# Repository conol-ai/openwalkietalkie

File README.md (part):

# Cohdl OpenWalkieTalkie

[Website and downloads](https://openwalkietalkie.org/) ·
[Latest release](https://github.com/conol-ai/openwalkietalkie/releases/latest)

Firmware and [routed BodyV5 r3 hardware design](hardware/rev-a/README.md) for
OpenWalkieTalkie, a handheld with a touch screen, a scroll wheel, PTT, Enter,
Esc, Shift and two front macro keys. The custom hardware includes a four-layer main PCB and
two-layer encoder PCB, with matching fabrication files and populated 3D models.

The firmware turns the device into the **Agent Command Deck**: a handheld
status board and radio for someone running several AI agent sessions at once.
The screen shows who needs you, PTT talks to the active agent, and the buttons
answer questions and switch channels.

The Rust / [embassy](https://embassy.dev) firmware currently runs on a **LilyGo
T-Display SF32** development board, which carries a SiFli **SF32LB52x** (Cortex-M33,
16MB NOR, 8MB PSRAM) and the same class of 2.16" CO5300 AMOLED with CST9220
touch. The dev board has no scroll wheel, so the **T-SF32-Keyboard** expansion
stands in for the wheel and buttons.

Sibling to [`openmicrokbd`](https://github.com/conol-ai/openmicrokbd) (v1,
STM32F072) — same approach, different silicon.

## What works today

Boot, the debug UART, the shared I2C bus, keypad and touchscreen input,
battery charging, and the Agent Command Deck's 480x480 UI on the AMOLED:
five faces, the face manager, notifications, the PTT LISTENING overlay and a
built-in demo host. Everything above the drivers is covered by host tests and
rendered previews; **none of the deck has been validated on hardware yet**
(see the [first-flash checklist](docs/deck-device-checklist.md)).

The deck is its own USB/BLE HID device: **Cohdl OpenWalkieTalkie**, VID
`0x1209` PID `0x5754`, one vendor collection (usage page `0xFF00`, report id
6, 64-byte reports). Report channel 2 carries a small system RPC
(`sys.version`, `sys.reboot`, `device.status`); the deck faces talk to a deck
host over channel 5 of the same connection ([deck protocol](#the-deck-host)).

The `1209:5754` allocation has been requested in
[pid.codes PR #1312](https://github.com/pidcodes/pidcodes.github.com/pull/1312)
and is pending registry approval. Application firmware and USB recovery use
the same product ID.

Pair **OpenWalkieTalkie** in macOS Bluetooth settings. The latest computer's bond
key and HID/battery notification preferences are stored in an append-only
flash journal at `0x12710000..0x1271FFFF`, reserved from the application
linker region. Automatic encrypted reconnection after a firmware update has
been verified. Upgrading from firmware that kept keys only in RAM requires
forgetting the old device and pairing once to create the persistent bond.

The journal checks each record's version and CRC, skips torn writes, and
verifies writes by reading them back. It supports 1024 changed records and
never erases flash; an exhausted journal reports a storage error. Unchanged
keys/preferences do not consume records. `tools/flash.sh` writes ELF load
segments and preserves the reserved journal. A whole-chip erase does not.
The Embassy target carries controls, deck traffic and battery status over HID.
On Rev A it also carries the microphone and speaker, as its own BLE GATT
service on the same link rather than as a Bluetooth audio device: a PTT press
streams 16 kHz IMA ADPCM to the host, and the host's spoken replies come back
the same way (`docs/deck-protocol.md`, "Voice"). Over the USB cable the same
frames ride report channel 7 of the HID collection, so a deck on the cable
alone has its voice too, with no pairing; `deckd` uses the cable whenever it
is there and Bluetooth otherwise. The
[native audio target](native/README.md) instead presents the display board's
microphone and speaker as Bluetooth Classic audio (HFP/A2DP) alongside the
same UI.
Both targets show the website's pixel-radio icon and stacked OpenWalkieTalkie
title on a black boot splash, with a small COHDL mark and “A COHDL PROJECT”
credit. After 1.2 seconds, the Agents face appears.
The same radio appears in Settings → About and in the Mac app, Dock, menu bar
and updater. Regenerate the desktop assets with `python3 tools/generate-branding.py`
(Pillow); normal builds use the checked-in images.

Embassy boot log, abridged:

```
SFBL
openwalkietalkie-fw 0.1.0
board: LilyGo T-Display SF32 (dev)
board: holding power rail (PA41)
board: bringing up I2C1 (SCL PA38 / SDA PA37) at 400000 Hz
display: CO5300 initialised (480x480, rotation=0deg)
board: display ready
board: ready
boot: OpenWalkieTalkie splash ready
boot: I2C1 before keyboard power-up:
  0x22 XL9555 GPIO expander (keyboard board)
  0x25 AW21009 keypad LED driver (keyboard board)
  0x34 TCA8418 keypad scanner (keyboard board)
app: Agent Command Deck ready
keypad: TCA8418 ready (5x4 matrix), PA11 interrupt + 50ms fallback
```

## Install on Omarchy (Linux)

On an [Omarchy](https://omarchy.org/) (Hyprland) laptop, the deck drives the
desktop and your coding agents with no Mac involved. It shows your
workspaces and windows on the Omarchy face, and your Claude Code, Codex and
Kimi Code sessions on the roster. A PTT press on a session types the
recognised words into its terminal. Two systemd user services do it:
`deckd`, built for Linux, and the Omarchy bridge in
[`host/omarchy/`](host/omarchy/README.md); the companion app, the same window
as on a Mac, goes in Omarchy's app launcher. There is no Linux download yet:
build from source (about ten minutes the first time). The step-by-step guide
is at [openwalkietalkie.org/docs/omarchy](https://openwalkietalkie.org/docs/omarchy/).

```sh
sudo pacman -S --needed base-devel git rustup cmake clang espeak-ng wtype
rustup default stable
git clone https://github.com/conol-ai/openwalkietalkie.git
cd openwalkietalkie/host
cargo build --release --target x86_64-unknown-linux-gnu -p deckd -p openwalkietalkie-app
sh omarchy/install.sh target/x86_64-unknown-linux-gnu/release/deckd \
    target/x86_64-unknown-linux-gnu/release/openwalkietalkie-app

# Once, as root: let deckd open the deck (USB-C and Bluetooth alike)
sudo install -m 644 omarchy/70-openwalkietalkie.rules /etc/udev/rules.d/
sudo udevadm control --reload && sudo udevadm trigger --subsystem-match=hidraw

# Put your sessions on the deck (sessions already open need a restart)
python3 omarchy/omarchy_hook.py install claude   # and codex, kimi
```

Then connect the deck with USB-C, or pair **OpenWalkieTalkie** over
Bluetooth, and check that the `link:` line says `Connected, session Live`
when you run `deckd status`, or open **OpenWalkieTalkie** from the app launcher.

- **Voice:** if Superwhisper (Omarchy's dictation) is set up, it recognises
  presses with no extra setup. Otherwise download the local Whisper model:
  see [Voice](host/omarchy/README.md#voice-ptt).
- **Macropad keys that trigger Omarchy's Super shortcuts** need
  `/dev/uinput`. `install.sh` prints the optional root steps.
- **Claude usage bars** on the Usage face:
  `deckd config set 'usage.providers=["codex","claude"]'`.

To update: `git pull`, build, and run `install.sh` again.

## Faces

The screen is a strip of faces, one on screen at a time. The default strip,
left to right: **Agents** (the agent-session roster, home), **Omarchy** (a
remote for the Omarchy/Hyprland desktop), **Macropad**, **Usage**, **System**, **Arcade** and
**Settings**.

- **Boot and home are the Agents face.** Until a deck host says hello the deck
  is empty and every face's header tag reads `offline`; a lost host leaves its
  data on screen, gray, tagged `offline`. Settings → Host → Demo data (off by
  default) fills the deck with built-in demo data instead, tagged `demo`, until
  the first real `hello` clears it.
- **SHIFT+SCROLL moves between faces**, one face per detent, clockwise to the
  right, with hard ends and no wrap. On the dev keypad: hold HOME and press ▼
  or ▲.
- **CANCEL at a face's top level goes home.**
- **Double-SHIFT** (two quick taps of HOME, nothing else in between) opens the
  face manager: reorder, add and remove faces (at most eight, three Macropads).
  Agents and Settings stay pinned.
- **PTT talks to an agent from work faces**, over a full-screen LISTENING
  overlay. On Arcade it is a local game button and never opens the microphone.
- **A new question or finished task raises a toast** for 4 seconds; tapping it
  jumps to the card. Unread notices wait in a drawer (swipe down from the top
  edge), flagged by a pill at the top of the screen, red while a question waits.
- **Idle-home:** after 120 seconds without local input the deck returns to the
  Agents roster (Settings → Display; off, 30, 60 or 120 seconds). It waits for
  a PTT session to end.
- **Sleep locks every local control, including PTT.** Any button, wheel detent
  or touch lights the lock screen. Turn the wheel counterclockwise four ticks
  to unlock; clockwise rotation resets progress. The unlocking ticks and any
  press or touch begun while locked never trigger the underlying screen.

[The Agent Command Deck](docs/agent-command-deck.md) is the full grammar: views,
cards, the manager, notifications, settings and the PTT session rules.

### Fonts

Deck text is Noto Sans (SIL Open Font License, `assets/fonts/`), rasterized
ahead of time into 4-bit glyph atlases by `tools/generate-ui-fonts.py`; the
firmware carries no font engine. The panel is small and dense (480 px over
38.8 mm, about 12 px/mm), so the type ramp runs about 1.6x the mockups' sizes:
15 px for hints, 18 px for tags and labels, 22 px body text, 25 px list rows and
up to 48 px for the big numbers (`RAMP` in `tools/generate-ui-fonts.py` and
`src/ui/theme.rs`). The mockups' layout rectangles are kept where the larger
text fits, and moved where it does not (the question card's choices start
lower; the PTT pill is wider). `tools/generate-ui-fonts.py --check`
regenerates into a temporary directory and diffs; the atlases depend on the
local FreeType build, so a check on another machine may differ.

Chinese and Japanese text fall back to Noto Sans CJK SC: 28,759 glyphs covering
simplified and traditional Chinese, Japanese kana and kanji, Extension A,
CJK punctuation, and fullwidth and halfwidth forms. A shared 26 px, 2-bit atlas
is filtered to each text size, keeping the firmware inside the board's
application partition. The host uses the same
metrics when wrapping messages. Regenerate it with
`python3 tools/generate-cjk-font.py` (or verify with `--check`); source,
license and coverage details are in `assets/fonts/gen/README.md`.

### The deck host

The deck faces are drawn from data a host daemon pushes over HID channel 5:
agents, cards, replies, transcripts, workspaces, macros and usage. The device
sends back keys, answers, PTT edges, channel switches and settings. The wire
contract is [docs/deck-protocol.md](docs/deck-protocol.md). The host is
[`deckd`](host/README.md), the Rust service in `host/`: today it owns the link
(hello, sync barrier, heartbeat, the paced outbox), a demo roster
(`deckd run --demo`) and its open API — JSON-RPC over a Unix socket and over
`127.0.0.1:47201` (HTTP, WebSocket, SSE), so a script or a `curl` one-liner can
be an agent on the deck and answer its own cards; the Claude Code and Codex
hook adapters, voice and the gpui GUI follow the plan in
[docs/host-service.md](docs/host-service.md) (status at its top; research in
[docs/host-research/](docs/host-research/)). `tools/deck-sim.py` remains the
reference host: it runs the mockup session against a device, `--dry-run` prints
the framed reports without hardware, and `tools/host-test.sh` diffs `deckd`'s
framing against it.

Version 0.11.0 adds native companions: Conol desktop conversations, a new-chat
launcher, multi-step questions, and actual model/effort reporting on the Mac and
deck. Both apps and the firmware need compatible builds. See the
[Conol integration notes](docs/conol-integration.md) and the public
[native companion guide](https://openwalkietalkie.org/docs/native-companions/).
Other apps can use the same API; the
[standalone Python example](host/examples/native_companion.py) runs scripted
conversations and forms without Conol or a model API key.

The deck's spoken replies are bring-your-own-key: give `deckd` an OpenAI or
ElevenLabs API key (on the app's Voice screen under *Spoken replies*, or
`deckd tts key set --provider openai`, typed without echo or piped in) and
the announcements are synthesised by that provider's model
(`gpt-4o-mini-tts`, `eleven_flash_v2_5`), streamed as it is generated; without
a key, Apple's synthesiser speaks on the Mac and nothing leaves the machine.
The key takes effect at the next announcement, no restart, and a provider that
refuses or a dead network falls back to Apple's voice. Or keep the voice on the
Mac: a Kokoro voice (Chinese and English, 103 speakers, a one-time 365 MB
download that the app offers at first start, or `deckd tts install`) speaks
entirely on the machine. `deckd tts status` says which is speaking. The
Qwen3-TTS sidecar (`[voice.tts] engine = "mlx"`, `deckd tts install --mlx`,
needs `uv`) remains available for its voice quality. Speech
recognition is Apple's on-device recogniser by default, and it too can be a
local model: opt in to Whisper (large-v3-turbo, a one-time 1.6 GB download
that the app offers at first start, or `deckd stt install`) and the deck
recognises Chinese and English in one utterance, still entirely on the Mac.
Nothing is downloaded until you say so.

The Usage face is fed by `deckd` itself, the way Zeron does it: the Claude
account's rate-limit windows come from Anthropic's `/api/oauth/usage` with the
Claude Code login (on macOS the `Claude Code-credentials` Keychain item, which
macOS asks about once — *Always Allow* keeps it quiet; a *Deny* leaves the
Claude bars empty), polled every five minutes, and the Codex account's from the
Codex app-server, which also pushes them after every turn. One bar per window
(`Claude session`, `Claude week`, `Codex session`, …) with the countdown to its
reset; ENTER on the face probes both at once. `[usage] providers` in
`config.toml` picks the providers, and a chained `deckd hook claude-statusline`
is read too when the operator has one.

### System Status

The deck's **System** face shows the connected Mac's CPU load, memory used / total,
GPU load and free / total startup-volume storage. `deckd` samples every two seconds;
the meters refresh only when their displayed values change. CPU load is normalized
across all cores, memory includes app, wired and compressed memory, and storage is
the writable startup data volume. GPU load comes from the graphics driver's IOKit
counters (the busiest accelerator when there is more than one).

Unavailable counters show **Not available**. After ten seconds without a sample,
the retained readings are gray and marked **STALE**; a lost host is **OFFLINE**.
The Mac app has no additional page. System follows Usage in a fresh default strip;
for a saved layout, double-tap Shift → **+** → **System** to add it. Matching
firmware and `deckd` are required; telemetry is not sent to older decks.

### Interface language

Choose **Service → Language** in the Mac app, or **Settings → Display →
Language** on the deck, to switch between **English**, **简体中文** (Simplified
Chinese), **繁體中文** (Traditional Chinese), and **日本語** (Japanese). On the
deck, press Enter on Language, turn the wheel, then press Enter to finish.
The interface changes immediately on both sides and remembers the choice
across restarts. English is the default.

Menus, controls, notifications, and the tutorial follow this choice. Agent
messages, custom names, and speech recognition keep their own language.
Choices made while the deck is disconnected sync when it reconnects. The
newer saved version wins; the app wins a tie. Language sync needs matching
updated firmware; the app keeps its own language choice with older decks.

### Timer and Pomodoro

Add **Timer** from the face manager's **+** gallery for a stopwatch, countdown
and **Pomodoro** timer. Use Left/Right or tap the tabs to choose a mode;
Enter starts, pauses or resumes. The countdown's wheel and preset buttons
set its length while idle.

Pomodoro alternates **25 minutes of focus** with **5-minute breaks**, with a
**15-minute break after four focus sessions**. Each completed phase waits
for **Next / Enter** before the next begins. Cancel resets the cycle. The
clocks keep running on other pages and while the screen sleeps; completion
wakes the screen and shows a toast that opens the right tab when tapped.
They work without a computer and last until the device restarts.

### Arcade

Three offline games with original pixel art and synthesized 8-bit music:

Gameplay uses the full 480×480 display with an overlaid score. Control hints
appear when starting or pausing; Enter pauses and Cancel returns to the game list.
Snake's corner walls follow the rounded panel so food always stays visible.

| Game | Controls |
| --- | --- |
| Flappy Bird | Tap PTT to fly; avoid pipes and the top/bottom edges. |
| Snake | Turn the wheel clockwise/right or counter-clockwise/left. Left/Right buttons also turn relative to the snake's heading. |
| Raiden (雷电) | Hold Left/Right to move; the plane fires automatically. Three lives. |

Use the wheel and Enter, or touch a menu row, to choose a game. Enter starts,
pauses, resumes or retries; Cancel returns to the game list. Shift+wheel still
changes faces. Leaving the game, opening an overlay or sleeping pauses it.
Best scores last until the device restarts.

**Arcade → Sound → Enter** cycles **Off → SFX only → Music + SFX** (touch works
too). Off is the default; volume follows the Speaker setting. The three original
music loops and seven effects are synthesized locally, with no recorded audio
assets. Pausing/leaving stops sound, host speech takes priority, and microphone
capture silences game audio. A connected app remembers the sound preference;
without the app it lasts for the current boot (the next boot starts Off).

Each tune has a 48-bar arrangement with an intro, theme, answering melodies,
a quieter middle, build and return: Flappy Bird runs 96 seconds, Snake 115.2
seconds and Raiden 76.8 seconds before repeating. Bass patterns, percussion
fills and pulse tones vary between sections. Pausing or retrying the same game
continues its music position; choosing a different game starts that game's tune.

Arcade is in the new default strip before Settings. For a previously saved
layout, double-tap Shift → **+** → **Arcade** to add it. Use matching firmware and
host builds: the wire vocabulary now includes `arcade` and `arcadesound`.

Silent development checks and previews:

```sh
python3 tools/preview-all.py --board hw-a --out target/arcade-preview arcade arcade-flappy arcade-snake arcade-raiden arcade-paused
cargo run --manifest-path native/core/Cargo.toml --example arcade-audio --locked --offline --target aarch64-apple-darwin --target-dir target/native-core-preview -- target/arcade-audio
```

The second command writes three BGM WAVs and seven SFX WAVs without opening an
audio device. These are review exports; the firmware runs the same synthesizer.

## The screen

**The screen mounting is chosen per board at build time.** The default build is
the upright LilyGo T-Display SF32 development board: no physical rotation. The
custom Rev A hardware mounts the panel upside down: build it with
`--features hw-a` (`OWT_BOARD=hw-a tools/build-native.sh` for the native
target), and the boot splash, UI pixels, partial-update windows and touch
coordinates turn 180° together. The shared switch is `ROTATE_180` in
`src/display/orientation.rs`. Both targets print the rotation in their boot
log, and Settings → About shows the board and rotation, so an image built for
the wrong board is easy to spot. `tools/test-all.sh` runs every test in both
configurations. The host UI preview stays upright. See
[rotation and animation validation](docs/display-performance.md#screen-mounting-and-animation).

`hw-a` is the whole Rev A pin map, not only the rotation (`src/board.rs` has
both tables): the panel's two rails are switched on through PA11 (logic) and
PA10 (4 V) before the CO5300 reset sequence, the touch controller sits on
I2C1 at PA42/PA41 with its reset on PA44 and interrupt on PA43, the six
buttons and the wheel are read from GPIOs (`src/input/gpio.rs`), the
MP34DT05 microphone is a PDM part on PA22/PA23 with its supply switched on
PA28 (both images capture it through PDM1; `src/audio/pdm.rs` here), the
NS4150B speaker amplifier is enabled on PA20 behind the SF32's audio DAC
(`src/audio/speaker.rs`), the USB-C
data pair reaches the SF32's own USB block on PA35/PA36 so `src/link/usb.rs`
serves the deck's HID device over the cable as well as over Bluetooth
(the host prefers the cable: it syncs in well under a second and writes a
report in about 0.7 ms where the BLE link needs about 360 ms; on an
Apple-silicon MacBook the first plug-in raises macOS's "Allow accessory to
connect?" prompt and the device stays unconfigured until it is allowed; see
`docs/deck-protocol.md`), and there
is no keypad and no I2C charger: the r6 board's BQ24073 charges on its own
and firmware cannot see its state, so the battery figure follows the voltage
curve in both directions at the usual 1 %/minute, never shows charging, and
100 means the top of the curve rather than a confirmed termination. The native
image follows the same switch through
`OWT_BOARD=hw-a tools/build-native.sh`, which also builds its C side for
Rev A.

`hw-b` is the **Rev B main board** (`hardware/rev-b`): it implies `hw-a`
and overlays the three pins that moved, which is the whole difference. The
NS4150B's enable is on PA1 (PA20 is unconnected), the CAL test pad TP3 is on
PA0 (parked as a pull-down input; set SiFli's calibration tool's signal pin
to PA00), and the BQ24073's CHG output reaches PA33, so Rev B shows
*charging* while the cell takes current and confirms a full charge the way
the dev board does (the pin going high with a USB host attached and the
cell at the charge voltage; on a charger-only supply the end of the charge
reads as no input and the figure holds). Build it with `--features hw-b`
(`OWT_BOARD=hw-b tools/build-native.sh` for the native image, which defines
`OWT_BOARD_HW_B` on the C side); a `hw-a` image boots on Rev B but its
speaker stays silent. Settings → About names the board, `sys.version`
reports it, and `tools/flash-usb.py` refuses an image built for another
board than the running deck reports (`--any-board` overrides). Rev B's UART
pads are the same three, so the first flash is the same procedure, with
the pogo jig in `hardware/rev-b/jig` instead of wires. The r6 board has no USB-serial bridge: `sftool` talks to UART1 on test
pads TP6 (RX) and TP8 (TX) with TP4 as ground. A DAPLink's UART side works
there with `--compat true`, because its USB CDC bridge drops sftool's 64 KiB
stub frame. A blank board needs the flash table and bootloader at
`0x12000000` before the app: `OWT_BOARD=hw-a OWT_BOOT_IMAGES=1
tools/build-native.sh` builds both from `native/boards/openwalkietalkie/ptab.yaml`
(`build_openwalkietalkie_hcpu/ftab.bin` for `0x12000000` and
`bootloader/output/bootloader.bin` for `0x12010000`), and a chip with no
flash table waits in the boot ROM's UART download monitor, so the first
flash involves no reset timing. Later flashes need none either: the debug
port answers while the firmware runs (after a soft power-off wake the deck
by holding PTT for 2 s first), and `tools/flash-uart.py <port>
write_flash --verify <elf>` clears a stale debug session first, hands the
port to sftool and lets it soft-reset the board into the new image. The
bring-up guide has the full procedure. With the `native/bootloader` image in
the bootloader slot (see below), the application also flashes over the
board's own USB-C port: `tools/flash-usb.py <elf>`.

## Touch, battery and rendering

The CST9220 at `0x5A` uses PA0 for reset and PA1 for its active-low interrupt.
Startup checks the controller identity, then enters normal reporting mode.
Each full 15-byte report from `0xD000` is acknowledged with `0xAB`; the marker
and contact count are checked before using coordinates. The driver
exposes one contact with down, move, up, and cancellation events; touch-controller
firmware is left intact. Interrupts wake input processing immediately, with
50ms idle and 20ms active touch fallback polling. The native driver also
latches falling interrupt edges while rendering or replying to the host.
Read failures, invalid or multi-finger reports,
and 120ms without fresh reports cancel the gesture and release held controls.

**Macropad keystrokes.** A Macropad key can carry a keystroke (`cmd+shift+4`),
set in the deck's own key editor (tap `+ assign`, or SHIFT+CANCEL on the
Macropad) or by the host; `deckd` posts it to the desktop through CoreGraphics
whenever the key is pressed. The deck is deliberately not a USB or Bluetooth
keyboard: the SF32LB52x USB block has one IN endpoint besides the control
endpoint, so a keyboard interface of its own cannot exist, and a keyboard
collection beside the vendor one would make macOS class the deck as a
keyboard that no ordinary program may open (Input Monitoring), `deckd` and the
flash tool included. So the daemon types for it, which needs the
**Accessibility** permission. The first refused key press makes macOS put its
own prompt up and list the process under System Settings → Privacy &
Security → Accessibility; switch it on there and the next press goes through
(the prompt names the *responsible* process, so for a `deckd` started from a
terminal that is the terminal's app). Until then the daemon logs each refused
keystroke, `perm.status` says `accessibility: "denied"`, and `perm.request
{which:"accessibility"}` asks again.

**Battery saving.** After 30 seconds without local input the screen dims; after
2 minutes it enters panel sleep and locks all local controls, including PTT.
Any button, wheel detent or touch lights a lock screen. Four consecutive
counterclockwise wheel ticks unlock it; clockwise rotation or another sleep
resets progress. All four ticks are consumed, and a button or touch begun
while locked must be released before a fresh action can be sent. A new deck
card lights the screen for 15 seconds without unlocking or counting as input.
Held controls keep an unlocked screen awake; a button trapped down while
locked does not prevent the display from dimming and sleeping again. The lit level
follows Settings → Display brightness 1–5 (panel 40/80/130/190/255); dim is 32,
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
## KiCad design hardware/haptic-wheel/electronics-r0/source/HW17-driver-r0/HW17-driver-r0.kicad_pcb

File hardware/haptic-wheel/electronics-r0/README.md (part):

# HW17 motor electronics R0

2026-10-30 · **Bench prototype, not a validated production release**

Two routed KiCad 10 boards for the custom three-phase, 12-slot / 14-pole wheel:

| Board | Construction | Function |
|---|---|---|
| HW17-driver-r0 | 50 × 40 mm, 2-layer FR4, 1.0 mm | DRV8311H, external 5 V supply, deck display-FPC interface |
| HW17-encoder-r0 | Ø5.5 mm central island, 1.6 mm flex tail | MT6701QT-STD absolute magnetic angle sensor, I²C |

The carrier stays outside the device for bench work. The encoder fits beneath the shaft magnet. The 31-pin OLED cable must be disconnected; the ordinary deck firmware cannot be used to drive this board. This package contains hardware and a firmware interface specification, **not motor-control firmware**.

## Files

- `source/HW17-driver-r0/HW17-driver-r0.kicad_pro`: carrier project; native schematic and routed PCB beside it.
- `source/HW17-encoder-r0/HW17-encoder-r0.kicad_pro`: encoder project.
- `source/HW17.pretty`: local footprints, including the unusual TI RRW-24 package and the host's actual FPC footprint.
- `fabrication/driver`, `fabrication/encoder`: Gerbers, Excellon drills, placement CSV, BOM and fabrication instructions.
- `review`: ERC/DRC/parity reports, mechanical check and visual review PDFs.
- `mechanical`: encoder STEP clearance envelopes and bare carrier STEP. The encoder model includes the stiffener, maximum chip and capacitor envelopes; copper, solder fillets and wires are not modeled. The carrier STEP is the bare PCB only.

Open the final projects named above. `-placed` and `-pre` files in the working repository are generation/routing intermediates, not fabrication masters. KiCad standard libraries are needed for library editing; the saved boards and schematics embed their geometry/symbols.

## Host interface

Verified against the actual Rev A r6 and Rev B main-board PCB netlists. J1 uses the same DIANWEI **8.03A5.031250**, 31-position, 0.3 mm pitch connector as host U3 (LCSC C55247264). Use a 0.2 mm FPC/FFC of the correct contact orientation. **Continuity-check every used pin end-to-end; do not infer pin mapping from the cable's appearance.**

| Host/display FPC pin → driver J1 | SF32 GPIO | Use |
|---|---|---|
| 4 | PA41 | Encoder SDA |
| 5 | PA42 | Encoder SCL |
| 8 | IO_3V3 rail | Sensor supply / logic pull-ups |
| 14 | PA9 | Driver enable through removable ARM jumper |
| 16 | PA5 | Phase U PWM |
| 17 | PA6 | Phase V PWM |
| 20 | PA7 | Phase W PWM |
| 21 | PA2 | nFAULT input, active low |
| 1, 7, 12, 22, 25, 28, 31, mounting pads | GND | Common signal / power reference |

All other FPC contacts are isolated on this carrier, including the display power rails and Rev B's pin-6 touch supply. PA5/6/7 support the SF32 timer pin-mux path; firmware must route three channels of one timer and configure synchronized PWM. Do not use three unrelated free-running timers. The stock display functions on these pins must be disabled first.

The host's 4-pin mechanical-encoder FPC is not used: it has two ground contacts and two filtered encoder inputs, with no supply contact. No phase-current ADC input is available on either host FPC. Therefore R0 supports angle feedback with **voltage-mode FOC**, not closed-loop phase-current regulation.

## External connections

| Connector | Pin order |
|---|---|
| J2, external supply | 1 = +5 V; 2 = GND |
| J3, sensor harness | 1 = GND; 2 = 3V3; 3 = SDA; 4 = SCL |
| J4, motor | 1 = U; 2 = V; 3 = W; star point stays inside motor |
| J5, ARM | 1 = enable command; 2 = driver nSLEEP; normally **no shunt** |
| J6, scope/external ADC | 1 = phase A current; 2 = B; 3 = C; 4 = CSAREF; 5 = GND |
| Encoder flex J1 lands | 1 = GND; **2 = SDA; 3 = SCL; 4 = VDD** |

**Sensor harness is not pin-for-pin:** carrier J3 → flex J1 is **1→1, 2→4, 3→2, 4→3**. Flex land numbering is in the KiCad board, placement drawing and wiring PDF. Land 1 is on the lower/left side of the tail when viewing the component side with the tail pointing upper-left. J1 on the flex is copper, not a purchased connector or pick-and-place part. Use short fine insulated wires, solder beyond the motor perimeter and strain-relieve them; do not attach a stiff cable directly to the sensing island.

## Driver circuit

- DRV8311**H**RRWR, hardware-interface variant; do not substitute P or S without redesign.
- MODE high: 3-PWM, 5 A driver overcurrent setting. INLA/B/C high enables all phases. GAIN high selects 2 V/A; SLEW low selects 35 V/µs.
- Separate external 5 V motor supply; SS14 reverse-input diode, SMAJ5.0A transient clamp, 100 µF bulk capacitor and local ceramics. VM is slightly below the external supply because of the diode. The TVS is not a continuous regenerative-energy sink.
- Driver AVDD is isolated from HOST_3V3. CSAREF uses AVDD through R12. Current-monitor nominal zero is CSAREF/2, with ±2 V/A response. Observe the datasheet's valid low-side conduction windows; these signals are not continuously valid DC phase-current measurements.
- 100 Ω series PWM resistors, 100 kΩ PWM pull-downs, 47 kΩ nSLEEP pull-down, and physical ARM isolation. nFAULT pulls up to host 3V3, not AVDD.
- The carrier is laid out for sub-amp bench experiments, **not 5 A continuous operation**. Some phase escape traces are 0.15 mm. The IC's 5 A OCP threshold does not protect the fine motor winding.

## Encoder and mechanical stack

MT6701QT-STD, QFN16 3 × 3 mm; MODE and CSN tied high for I²C. 7-bit address **0x06**. Read registers **0x03 then 0x04** in one transaction: `angle14 = (reg03 << 6) | (reg04 >> 2)`; mechanical radians = `angle14 * 2π / 16384`. There are 7 motor pole pairs; electrical angle requires measured direction and zero offset. Do not program EEPROM during normal testing.

The driver has 4.7 kΩ SDA/SCL pull-ups. With the host's existing 10 kΩ pull-ups the effective value is approximately 3.2 kΩ. Start at 100 kHz, verify edges, then try 400 kHz. Measure loop timing before choosing the final control bandwidth.

Mechanical coordinates use shaft center X=Y=0, carrier underside Z=0:

- Flex: nominal 0.15 mm finished thickness, Z=0.25…0.40 mm; tail width 1.6 mm, end radius 11 mm.
- Central PI stiffener including adhesive: nominal 0.25 mm, Ø5.5 mm. Finished island **0.40 mm maximum**; supplier must agree to a 0.36…0.40 mm stack and keep the top surface flat.
- Chip maximum 3.1 × 3.1 × 0.8 mm, plus 0.05 mm solder allowance: top Z=1.25 mm.
- 0201 capacitor body maximum 0.65 × 0.35 × 0.35 mm, center CAD (0, +2.25); check package substitutions against the Ø5 mm carrier bore.
- Shaft magnet: existing Ø4 × 0.5 mm, diametrical two-pole magnet, bottom Z=1.88 mm. Nominal chip-top gap **0.63 mm**. This gap does not establish adequate field strength or immunity to the motor magnets; those need measurement.
- Original HW17-R0 tail direction is +135°. The separate `-120deg.step` envelope is rotated −15° for the HW18-B1 carrier channel; rotate the complete PCB, then recalibrate encoder zero. The carrier files and hashes used in the interference checks are recorded in `review/mechanical-check.json`.
- Flex stack sits higher in the channel than the old generic rigid-flex tail placeholder, but remains within its 0.40 mm channel height. Nominal solid interference with both checked carriers is zero. Production tolerance and wire routing still need physical validation.

The MT6701 datasheet does not assign an electrical function to its exposed paddle. R0 solders it to an **isolated** copper island; obtain manufacturer confirmation of the paddle treatment before a production order.

## First-power sequence

1. Inspect QFN soldering, FPC orientation, flex wiring and resistance between all rails. Keep ARM shunt removed and motor disconnected.
2. Connect the deck with OLED unplugged. Load dedicated bench firmware that initializes nSLEEP low, PWM outputs safely, and nFAULT as an input. Do not fit ARM while the normal display firmware is running.
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
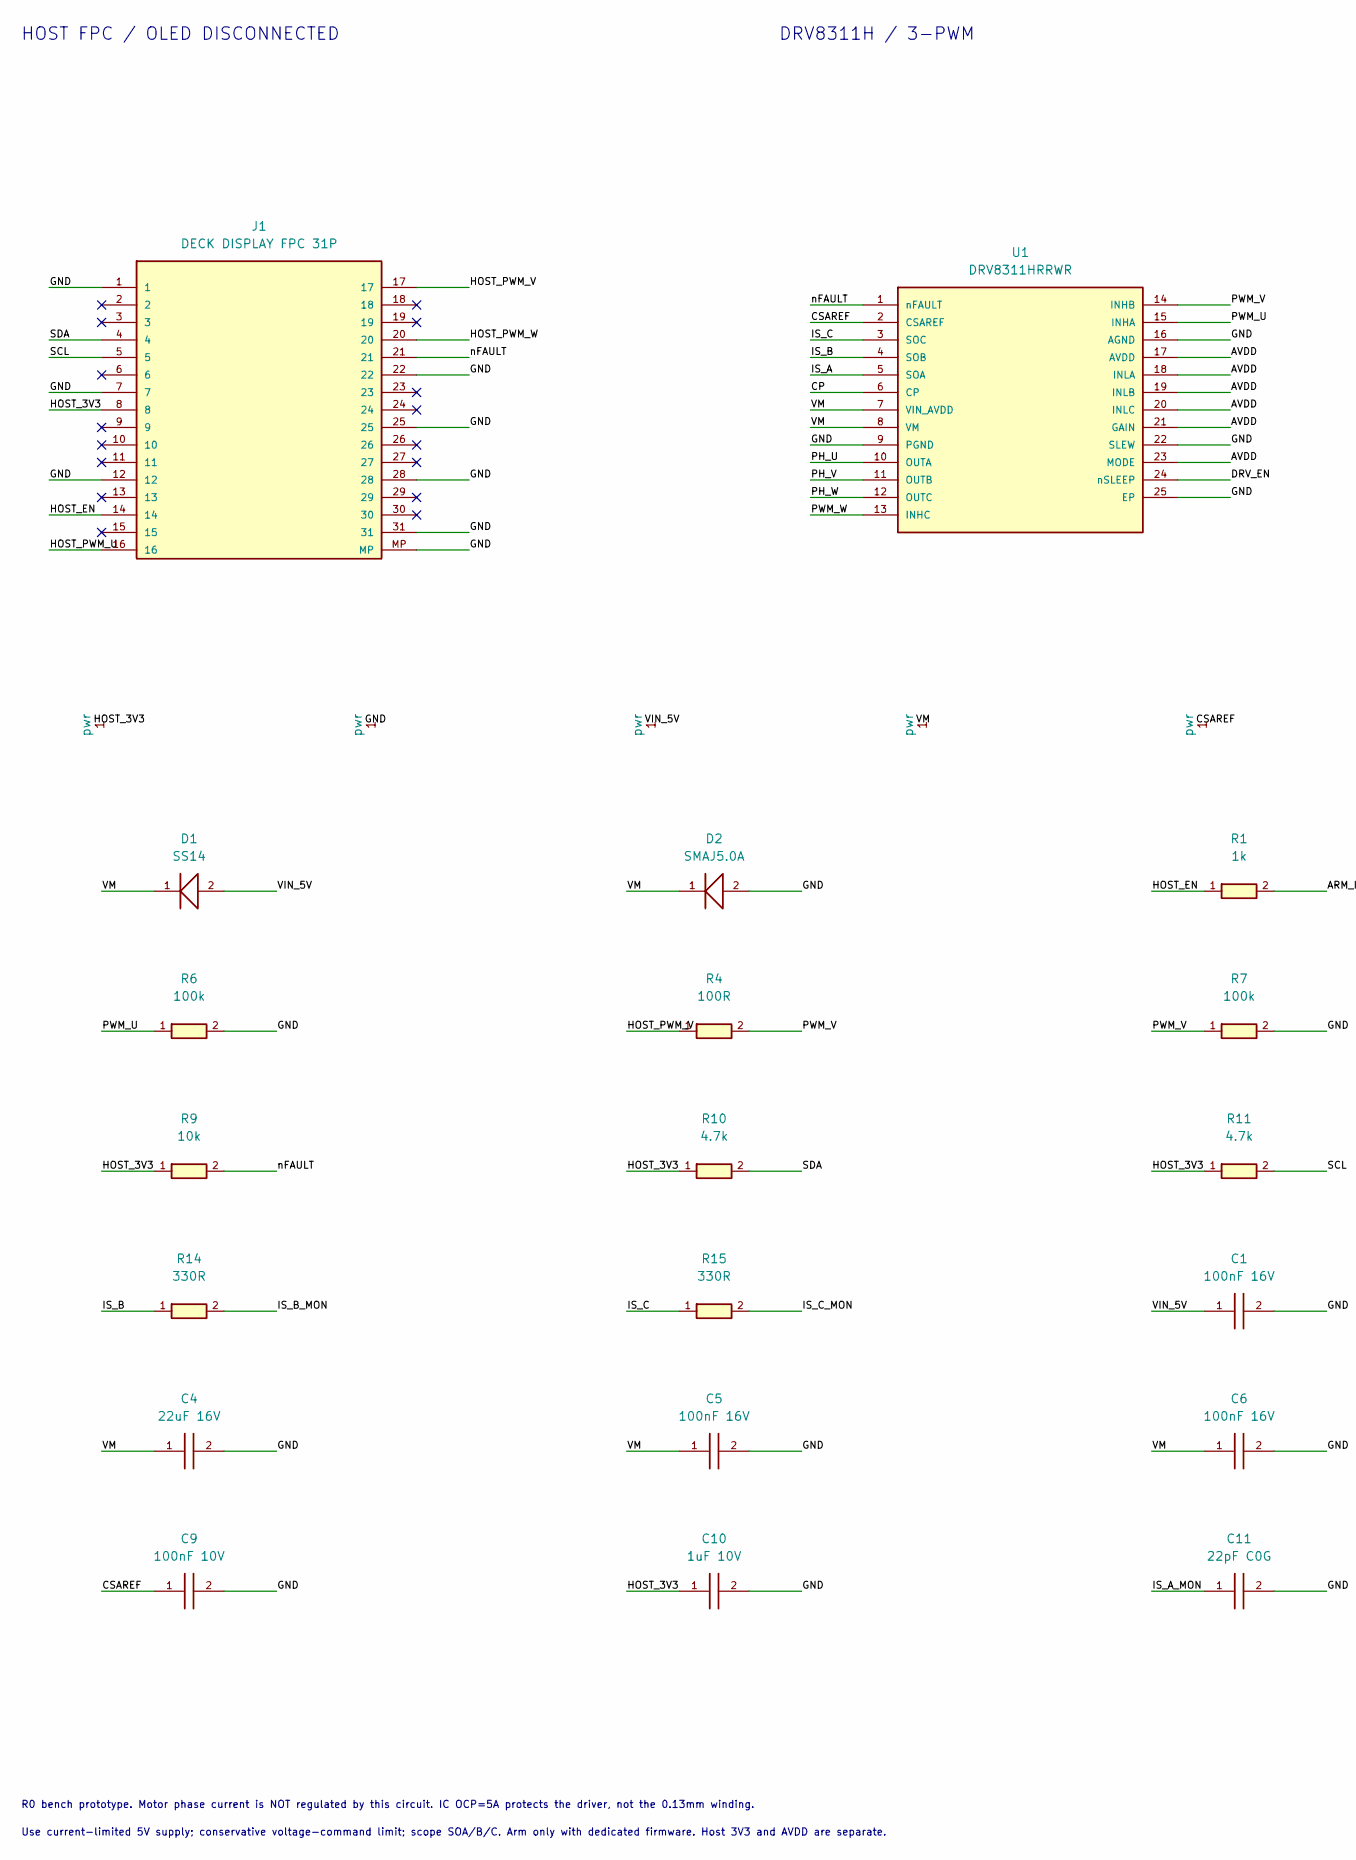
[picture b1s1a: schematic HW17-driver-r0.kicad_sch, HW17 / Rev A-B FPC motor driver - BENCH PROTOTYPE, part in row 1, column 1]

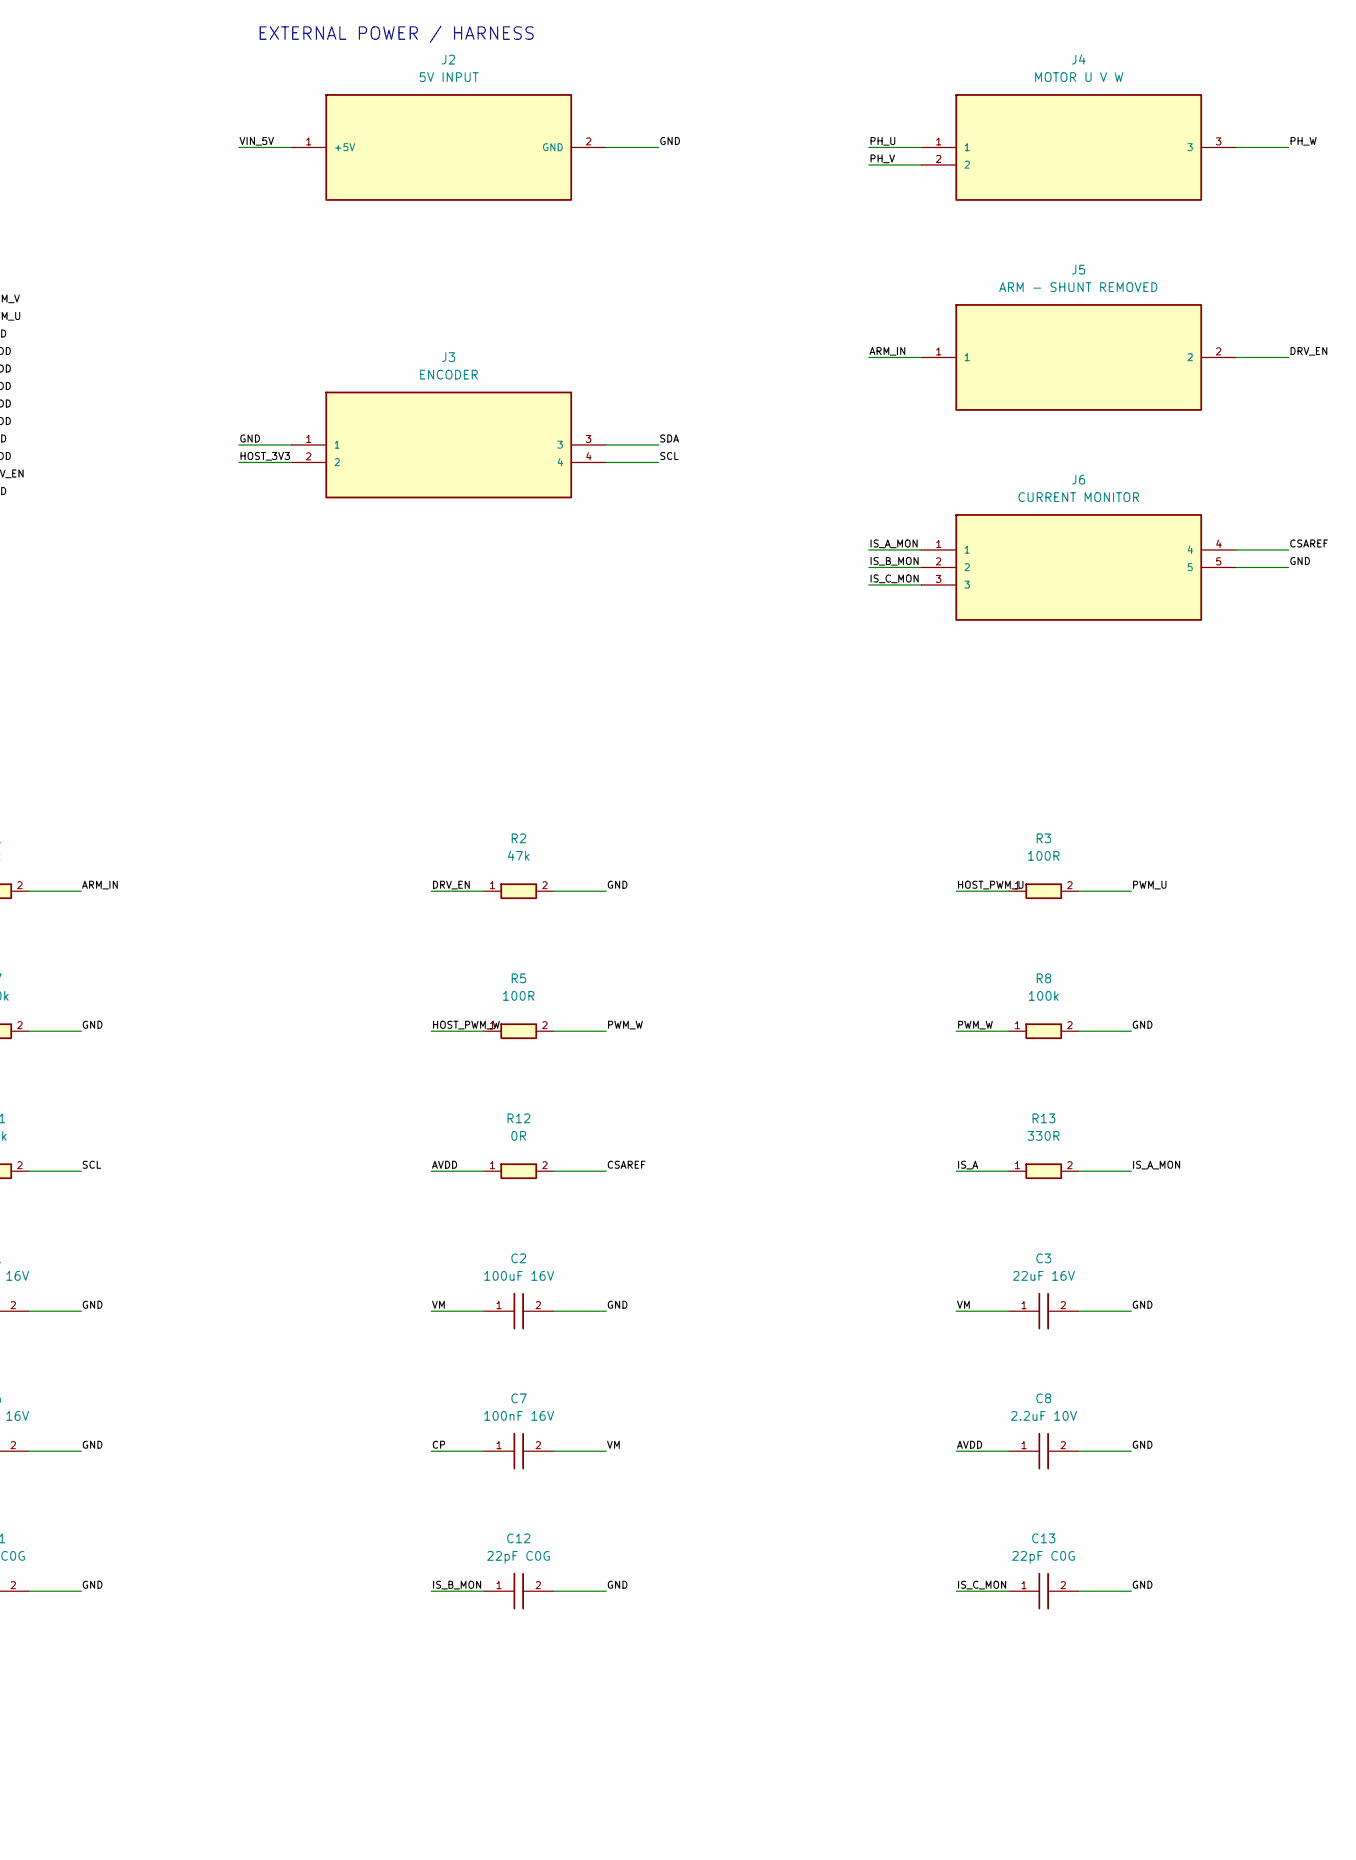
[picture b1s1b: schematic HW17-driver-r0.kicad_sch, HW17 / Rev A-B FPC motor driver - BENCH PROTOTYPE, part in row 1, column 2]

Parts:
C1, C5, C6, C7: 100nF 16V; C_0603_1608Metric
C2: 100uF 16V; CP_Radial_D6.3mm_P2.50mm
C3, C4: 22uF 16V; C_1206_3216Metric
C8: 2.2uF 10V; C_0603_1608Metric
C9: 100nF 10V; C_0603_1608Metric
C10: 1uF 10V; C_0603_1608Metric
C11, C12, C13: 22pF C0G; C_0603_1608Metric
D1: SS14; D_SMA
D2: SMAJ5.0A; D_SMA
J1: DECK DISPLAY FPC 31P; FPC31_DIANWEI_8_03A5_031250
J2: 5V INPUT; PinHeader_1x02_P2.54mm_Vertical
J3: ENCODER; PinHeader_1x04_P2.54mm_Vertical
J4: MOTOR U V W; PinHeader_1x03_P2.54mm_Vertical
J5: ARM - SHUNT REMOVED; PinHeader_1x02_P2.54mm_Vertical
J6: CURRENT MONITOR; PinHeader_1x05_P2.54mm_Vertical
R1: 1k; R_0603_1608Metric
R2: 47k; R_0603_1608Metric
R3, R4, R5: 100R; R_0603_1608Metric
R6, R7, R8: 100k; R_0603_1608Metric
R9: 10k; R_0603_1608Metric
R10, R11: 4.7k; R_0603_1608Metric
R12: 0R; R_0603_1608Metric
R13, R14, R15: 330R; R_0603_1608Metric
U1: DRV8311HRRWR; DRV8311_RRW0024A

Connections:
/ARM_IN: J5.1, R1.2
/AVDD: C8.1, R12.1, U1.17 (AVDD), U1.18 (INLA), U1.19 (INLB), U1.20 (INLC), U1.21 (GAIN), U1.23 (MODE)
/CP: C7.1, U1.6 (CP)
/CSAREF: C9.1, J6.4, R12.2, U1.2 (CSAREF)
/DRV_EN: J5.2, R2.1, U1.24 (nSLEEP)
/GND: C1.2, C2.2, C3.2, C4.2, C5.2, C6.2, C8.2, C9.2, C10.2, C11.2, C12.2, C13.2, D2.2, J1.1, J1.7, J1.12, J1.22, J1.25, J1.28, J1.31, J1.MP, J2.2 (GND), J3.1, J6.5, R2.2, R6.2, R7.2, R8.2, U1.9 (PGND), U1.16 (AGND), U1.22 (SLEW), U1.25 (EP)
/HOST_3V3: C10.1, J1.8, J3.2, R9.1, R10.1, R11.1
/HOST_EN: J1.14, R1.1
/HOST_PWM_U: J1.16, R3.1
/HOST_PWM_V: J1.17, R4.1
/HOST_PWM_W: J1.20, R5.1
/IS_A: R13.1, U1.5 (SOA)
/IS_A_MON: C11.1, J6.1, R13.2
/IS_B: R14.1, U1.4 (SOB)
/IS_B_MON: C12.1, J6.2, R14.2
/IS_C: R15.1, U1.3 (SOC)
/IS_C_MON: C13.1, J6.3, R15.2
/PH_U: J4.1, U1.10 (OUTA)
/PH_V: J4.2, U1.11 (OUTB)
/PH_W: J4.3, U1.12 (OUTC)
/PWM_U: R3.2, R6.1, U1.15 (INHA)
/PWM_V: R4.2, R7.1, U1.14 (INHB)
/PWM_W: R5.2, R8.1, U1.13 (INHC)
/SCL: J1.5, J3.4, R11.2
/SDA: J1.4, J3.3, R10.2
/VIN_5V: C1.1, D1.2, J2.1 (+5V)
/VM: C2.1, C3.1, C4.1, C5.1, C6.1, C7.2, D1.1, D2.1, U1.7 (VIN_AVDD), U1.8 (VM)
/nFAULT: J1.21, R9.2, U1.1 (nFAULT)

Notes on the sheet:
HOST FPC / OLED DISCONNECTED
DRV8311H / 3-PWM
EXTERNAL POWER / HARNESS
R0 bench prototype. Motor phase current is NOT regulated by this circuit. IC OCP=5A protects the driver, not the 0.13mm winding.
Use current-limited 5V supply; conservative voltage-command limit; scope SOA/B/C. Arm only with dedicated firmware. Host 3V3 and AVDD are separate.

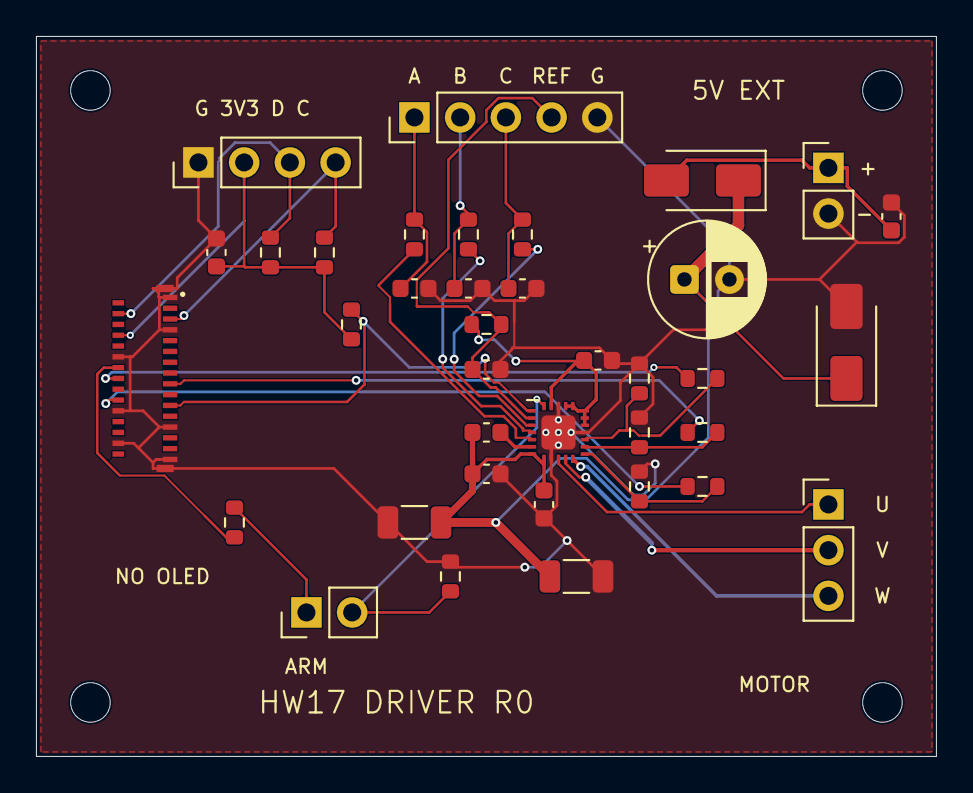
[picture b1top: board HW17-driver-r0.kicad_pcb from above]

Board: 2 copper layers, 50.0 x 40.0 mm, 41 parts (0 on the bottom side), 28 nets.

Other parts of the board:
H6, H40, H50, H84: MountingHole_2.2mm_M2

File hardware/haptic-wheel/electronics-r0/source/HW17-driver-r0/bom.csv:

Reference,Value,Footprint,MPN,LCSC,Quantity,Notes
J1,DECK DISPLAY FPC 31P,HW17:FPC31_DIANWEI_8_03A5_031250,8.03A5.031250,C55247264,1,31P 0.3mm; 0.2mm FPC; match host pin 1 to adapter pin 1. OLED disconnected.
U1,DRV8311HRRWR,HW17:DRV8311_RRW0024A,DRV8311HRRWR,C5218862,1,3PWM; GAIN=2V/A; SLEW=35V/us; OCP=5A (not motor-safe current regulation).
J2,5V INPUT,Connector_PinHeader_2.54mm:PinHeader_1x02_P2.54mm_Vertical,,,1,External current-limited bench supply only; no connection to host power rails.
J3,ENCODER,Connector_PinHeader_2.54mm:PinHeader_1x04_P2.54mm_Vertical,,,1,
J4,MOTOR U V W,Connector_PinHeader_2.54mm:PinHeader_1x03_P2.54mm_Vertical,,,1,
J5,ARM - SHUNT REMOVED,Connector_PinHeader_2.54mm:PinHeader_1x02_P2.54mm_Vertical,,,1,Fit removable shunt only after bench firmware initializes. No shunt in shipped assembly.
J6,CURRENT MONITOR,Connector_PinHeader_2.54mm:PinHeader_1x05_P2.54mm_Vertical,,,1,For oscilloscope/external ADC; NOT connected to SF32 ADC.
D1,SS14,Diode_SMD:D_SMA,SS14,C2480,1,
D2,SMAJ5.0A,Diode_SMD:D_SMA,SMAJ5.0A,,1,"Unidirectional 5V-standoff TVS; limits bus transients, not a sustained braking load."
R1,1k,Resistor_SMD:R_0603_1608Metric,RC0603FR-071KL,,1,
R2,47k,Resistor_SMD:R_0603_1608Metric,RC0603FR-0747KL,,1,
R3,100R,Resistor_SMD:R_0603_1608Metric,RC0603FR-07100RL,,1,
R6,100k,Resistor_SMD:R_0603_1608Metric,RC0603FR-07100KL,,1,
R4,100R,Resistor_SMD:R_0603_1608Metric,RC0603FR-07100RL,,1,
R7,100k,Resistor_SMD:R_0603_1608Metric,RC0603FR-07100KL,,1,
R5,100R,Resistor_SMD:R_0603_1608Metric,RC0603FR-07100RL,,1,
R8,100k,Resistor_SMD:R_0603_1608Metric,RC0603FR-07100KL,,1,
R9,10k,Resistor_SMD:R_0603_1608Metric,RC0603FR-0710KL,,1,
R10,4.7k,Resistor_SMD:R_0603_1608Metric,RC0603FR-074K7L,,1,
R11,4.7k,Resistor_SMD:R_0603_1608Metric,RC0603FR-074K7L,,1,
R12,0R,Resistor_SMD:R_0603_1608Metric,,,1,
R13,330R,Resistor_SMD:R_0603_1608Metric,RC0603FR-07330RL,,1,
R14,330R,Resistor_SMD:R_0603_1608Metric,RC0603FR-07330RL,,1,
R15,330R,Resistor_SMD:R_0603_1608Metric,RC0603FR-07330RL,,1,
C1,100nF 16V,Capacitor_SMD:C_0603_1608Metric,,,1,
C2,100uF 16V,Capacitor_THT:CP_Radial_D6.3mm_P2.50mm,,,1,C2 pin 1 positive.
C3,22uF 16V,Capacitor_SMD:C_1206_3216Metric,,,1,
C4,22uF 16V,Capacitor_SMD:C_1206_3216Metric,,,1,
C5,100nF 16V,Capacitor_SMD:C_0603_1608Metric,,,1,
C6,100nF 16V,Capacitor_SMD:C_0603_1608Metric,,,1,
C7,100nF 16V,Capacitor_SMD:C_0603_1608Metric,,,1,
C8,2.2uF 10V,Capacitor_SMD:C_0603_1608Metric,,,1,
C9,100nF 10V,Capacitor_SMD:C_0603_1608Metric,,,1,
C10,1uF 10V,Capacitor_SMD:C_0603_1608Metric,,,1,
C11,22pF C0G,Capacitor_SMD:C_0603_1608Metric,,,1,
C12,22pF C0G,Capacitor_SMD:C_0603_1608Metric,,,1,
C13,22pF C0G,Capacitor_SMD:C_0603_1608Metric,,,1,

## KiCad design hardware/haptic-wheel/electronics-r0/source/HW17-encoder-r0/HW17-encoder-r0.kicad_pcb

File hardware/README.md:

# OpenWalkieTalkie hardware

Board, case and fixture designs for the OpenWalkieTalkie deck. `rev-a/` holds
the BodyV5/BodyV6 lineage (r3 to r6) together with the case CAD and component
evidence; `rev-b/` is the current re-placed main board and its UART flash jig;
`rev-c/` is the same board on current CoHDL and library versions, with the
order data produced through CoHDL supplier bindings (copper unchanged).

## License

Copyright (c) 2026 Tony Huang.

This source describes Open Hardware and is licensed under the CERN-OHL-P v2.
You may redistribute and modify this documentation and make products using it
under the terms of the CERN-OHL-P v2 (https://ohwr.org/cern_ohl_p_v2.txt).
This documentation is distributed WITHOUT ANY EXPRESS OR IMPLIED WARRANTY,
INCLUDING OF MERCHANTABILITY, SATISFACTORY QUALITY AND FITNESS FOR A
PARTICULAR PURPOSE. Please see the CERN-OHL-P v2 for applicable conditions.

The full text is in [LICENSE](LICENSE); the SPDX identifier is
`CERN-OHL-P-2.0`. It covers everything that describes the device itself: the
CoHDL schematic sources, KiCad schematics and layouts, Gerbers and drill files,
bills of materials and placement files, the case and fixture CAD (`.f3d`,
`.step`, `.dxf`), fit assemblies, renders, drawings, and the release notes that
document them. It is a permissive licence: you may build, modify and sell
products from these files, including commercially, as long as you keep the
copyright and licence notices and do not use the project's names or marks to
imply endorsement.

It does not cover:

- **Software.** The scripts and tooling in this tree (`rev-a/check.sh`,
  `rev-a/validate_release.py` and every `scripts/` directory) are software and
  stay under the repository's MIT license, see [../LICENSE](../LICENSE). Each
  file carries an `SPDX-License-Identifier: MIT` header.
- **Third-party material.** Vendor CAD, datasheets, drawings and KiCad library
  models keep their own copyrights and licenses. See each release's
  `models/ATTRIBUTION.md`, `rev-a/mechanical-source/vendor/` and the
  provenance manifests next to them. Nothing here relicenses them.

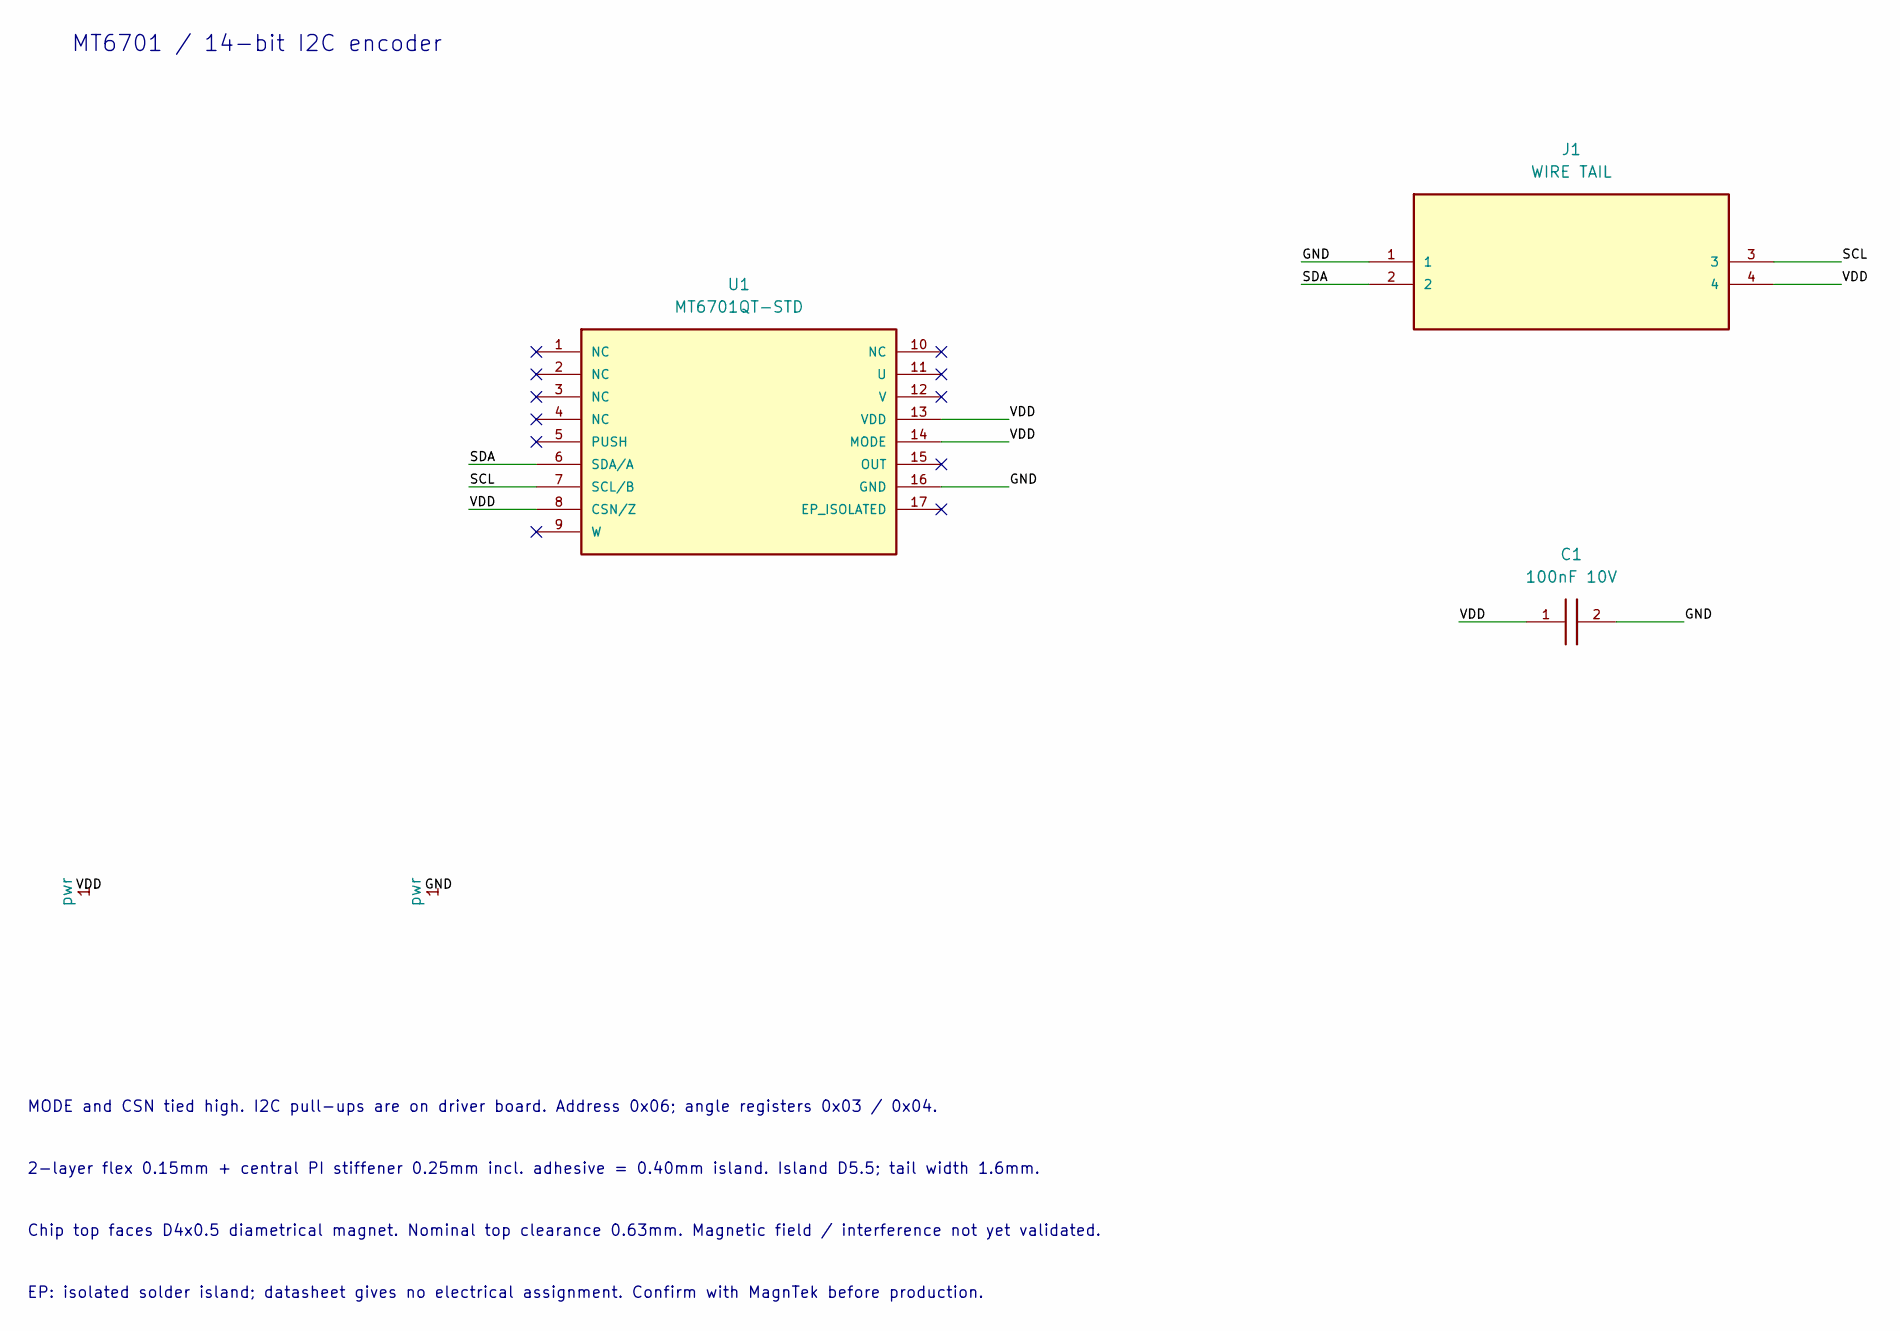
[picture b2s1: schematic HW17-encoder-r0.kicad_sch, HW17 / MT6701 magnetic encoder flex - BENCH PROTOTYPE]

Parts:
C1: 100nF 10V; C_0201_0603Metric
J1: WIRE TAIL; Flex_Tail_4_SolderPads_P0p35
U1: MT6701QT-STD; MT6701QT_QFN16_3x3_P0p5

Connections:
/GND: C1.2, J1.1, U1.16 (GND)
/SCL: J1.3, U1.7 (SCL/B)
/SDA: J1.2, U1.6 (SDA/A)
/VDD: C1.1, J1.4, U1.8 (CSN/Z), U1.13 (VDD), U1.14 (MODE)

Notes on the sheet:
MT6701 / 14-bit I2C encoder
MODE and CSN tied high. I2C pull-ups are on driver board. Address 0x06; angle registers 0x03 / 0x04.
2-layer flex 0.15mm + central PI stiffener 0.25mm incl. adhesive = 0.40mm island. Island D5.5; tail width 1.6mm.
Chip top faces D4x0.5 diametrical magnet. Nominal top clearance 0.63mm. Magnetic field / interference not yet validated.
EP: isolated solder island; datasheet gives no electrical assignment. Confirm with MagnTek before production.

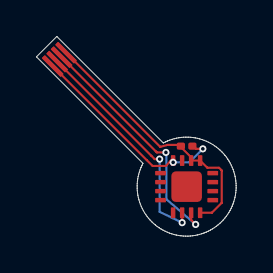
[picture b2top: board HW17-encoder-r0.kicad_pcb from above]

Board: 2 copper layers, 11.1 x 11.1 mm, 3 parts (0 on the bottom side), 4 nets.

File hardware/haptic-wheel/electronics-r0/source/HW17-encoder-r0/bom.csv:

Reference,Value,Footprint,MPN,LCSC,Quantity,Notes
U1,MT6701QT-STD,HW17:MT6701QT_QFN16_3x3_P0p5,MT6701QT-STD,C2913974,1,MODE and CSN tied VDD for I2C. EP soldered to isolated island; confirm EP policy with manufacturer.
C1,100nF 10V,Capacitor_SMD:C_0201_0603Metric,,,1,

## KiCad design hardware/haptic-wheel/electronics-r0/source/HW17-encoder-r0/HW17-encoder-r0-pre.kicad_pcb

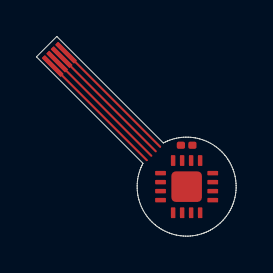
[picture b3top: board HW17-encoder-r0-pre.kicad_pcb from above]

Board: 2 copper layers, 11.1 x 11.1 mm, 3 parts (0 on the bottom side), 4 nets.

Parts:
C1: 100nF 10V; C_0201_0603Metric
J1: WIRE TAIL; Flex_Tail_4_SolderPads_P0p35
U1: MT6701QT-STD; MT6701QT_QFN16_3x3_P0p5

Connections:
GND: C1.2, J1.1, U1.16
SCL: J1.4, U1.7
SDA: J1.3, U1.6
VDD: C1.1, J1.2, U1.8, U1.13, U1.14

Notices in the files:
README.md:
License:
The software is MIT — see [LICENSE](LICENSE). That is everything outside
`hardware/` (firmware, native image, host crates, tools, packaging) plus the
scripts inside `hardware/`, which carry `SPDX-License-Identifier: MIT` headers.
The hardware and mechanical design is CERN-OHL-P-2.0 (the permissive CERN
Open Hardware Licence) — see [hardware/LICENSE](hardware/LICENSE) and
[hardware/README.md](hardware/README.md) for what that covers (CoHDL and KiCad
sources, fabrication outputs, BOMs, case and jig CAD).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
